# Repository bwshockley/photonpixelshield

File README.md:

Photon Pixel Shield
Photon Pixel Shield
========
The photon pixel shield is a small board for interfacing between a [particle.io](https://www.particle.io/) photon and some WS2812 based LED strips.  Specifically, this board was made to drive [Neopixel](https://www.adafruit.com/category/168) strips.

Power Requirements - Diode and Fuse Sizing
--------
The board takes in 5V only  and is used to power the photon and the pixel strip.  Please note that current requirements are mostly driven by the number of LEDs being driven.  Each WS2812 LED uses an estimate of 20mA, which can add up quickly.

50   Neopixels: 1A
100 Neopixels: 2A

You will need to pick your own diode and fuse.  Since these devices are through hole, physical sizing isn't as much of a concern for finding the right part - mostly the current/voltage ratings.  I found fuses and diodes up to 3A easily fit.  Find a Diode with a low forward voltage (less than 0.5V)

_Note that v6 does away with the diode, so no need to pick or size that and v7 does away with both the diode and fuse._

Digital Control
--------
The WS2812 based LED strips can be controlled via the photon and the [Neopixel library](https://github.com/technobly/SparkCore-NeoPixel) from Adafruit built by technobly.  No digital pin is selected by default on the board.  Pin D2 is the default in the library.  To use the default connect the solder jumper for D2 on the back of the board.  Otherwise, you may select almost any digital pin in both software on through the jumper on the board.

BOM
--------
The majority of the [BOM](http://www.mouser.com/ProjectManager/ProjectDetail.aspx?AccessID=84ec81cb7a), which as of 12-JUL-18, can be found on Mouser.com for around $3.50.  You will need to pick a diode and re-settable fuse as noted above.

Power LED
--------
A simple 3mm power LED is required if you wish to have a power indicator.  The resistor marked RLED on the board is for the LED.  Populate with an appropriate resistor value for the LED chosen.  You can use [this calculate](http://ledcalc.com) for sizing the resistor.

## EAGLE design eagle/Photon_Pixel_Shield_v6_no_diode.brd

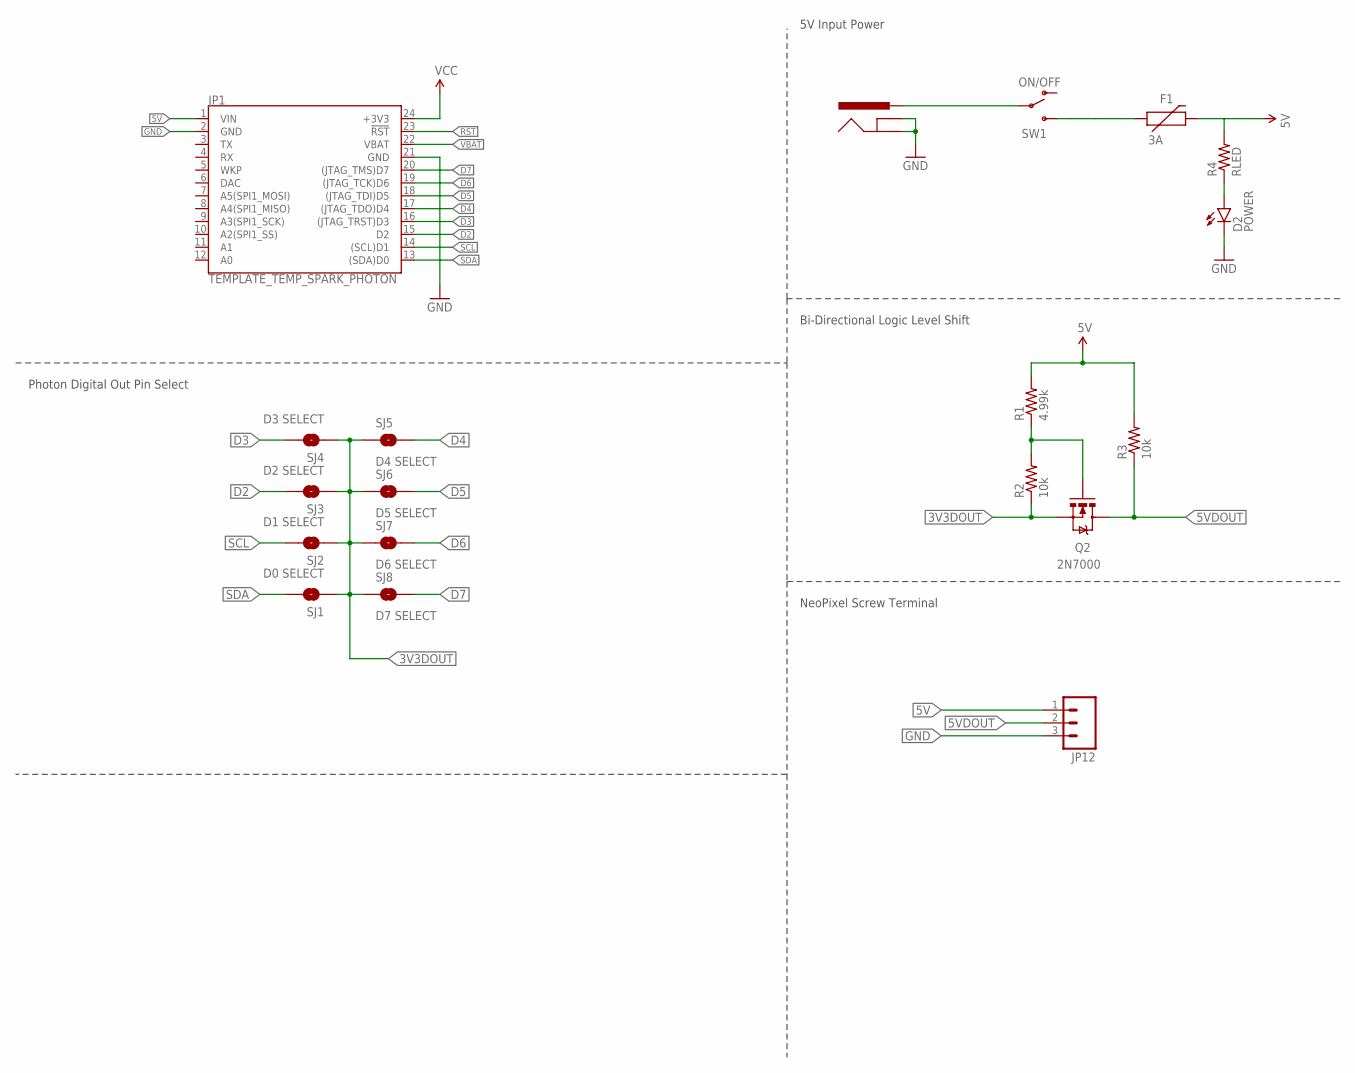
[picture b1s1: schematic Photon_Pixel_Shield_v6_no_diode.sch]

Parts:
D2: POWER; LED3MM
F1: 3A; PTC
J1: POWER_JACKPTH; POWER_JACK_PTH
JP1: TEMPLATE_TEMP_SPARK_PHOTON
JP12: M03SCREW; SCREWTERMINAL-3.5MM-3
Q2: 2N7000; TO-92
R1: 4.99k; AXIAL-0.3
R2, R3: 10k; AXIAL-0.3
R4: RLED; AXIAL-0.3
SJ1: D0 SELECT; SJ_2S-NO
SJ2: D1 SELECT; SJ_2S-NO
SJ3: D2 SELECT; SJ_2S-NO
SJ4: D3 SELECT; SJ_2S-NO
SJ5: D4 SELECT; SJ_2S-NO
SJ6: D5 SELECT; SJ_2S-NO
SJ7: D6 SELECT; SJ_2S-NO
SJ8: D7 SELECT; SJ_2S-NO
SW1: ON/OFF; SWITCH-SPST

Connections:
3V3DOUT: Q2.1 (S), R2.P$1 (1), SJ1.1, SJ2.1, SJ3.1, SJ4.1, SJ5.1, SJ6.1, SJ7.1, SJ8.1
5V: F1.P$2 (2), JP1.1 (VIN), JP12.1, R1.P$2 (2), R3.P$2 (2), R4.P$2 (2)
5VDOUT: JP12.2, Q2.3 (D), R3.P$1 (1)
D2: JP1.15 (D2), SJ3.2
D3: JP1.16 ((JTAG_TRST)D3), SJ4.2
D4: JP1.17 ((JTAG_TDO)D4), SJ5.2
D5: JP1.18 ((JTAG_TDI)D5), SJ6.2
D6: JP1.19 ((JTAG_TCK)D6), SJ7.2
D7: JP1.20 ((JTAG_TMS)D7), SJ8.2
GND: D2.K (C), J1.GND, J1.GNDBREAK, JP1.2 (GND), JP1.21 (GND), JP12.3
unnamed: F1.P$1 (1), SW1.3 (S)
unnamed: J1.PWR, SW1.2
unnamed: D2.A, R4.P$1 (1)
unnamed: Q2.2 (G), R1.P$1 (1), R2.P$2 (2)
RST: JP1.23 (!RST!)
SCL: JP1.14 ((SCL)D1), SJ2.2
SDA: JP1.13 ((SDA)D0), SJ1.2
VBAT: JP1.22 (VBAT)
VCC: JP1.24 (+3V3)

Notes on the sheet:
Bi-Directional Logic Level Shift
NeoPixel Screw Terminal
5V Input Power
Photon Digital Out Pin Select

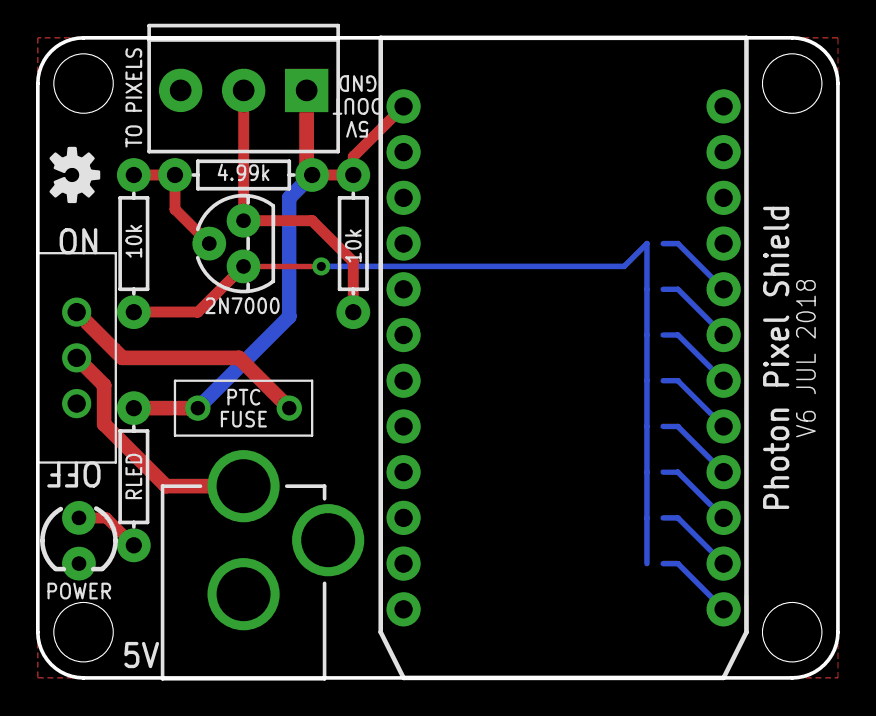
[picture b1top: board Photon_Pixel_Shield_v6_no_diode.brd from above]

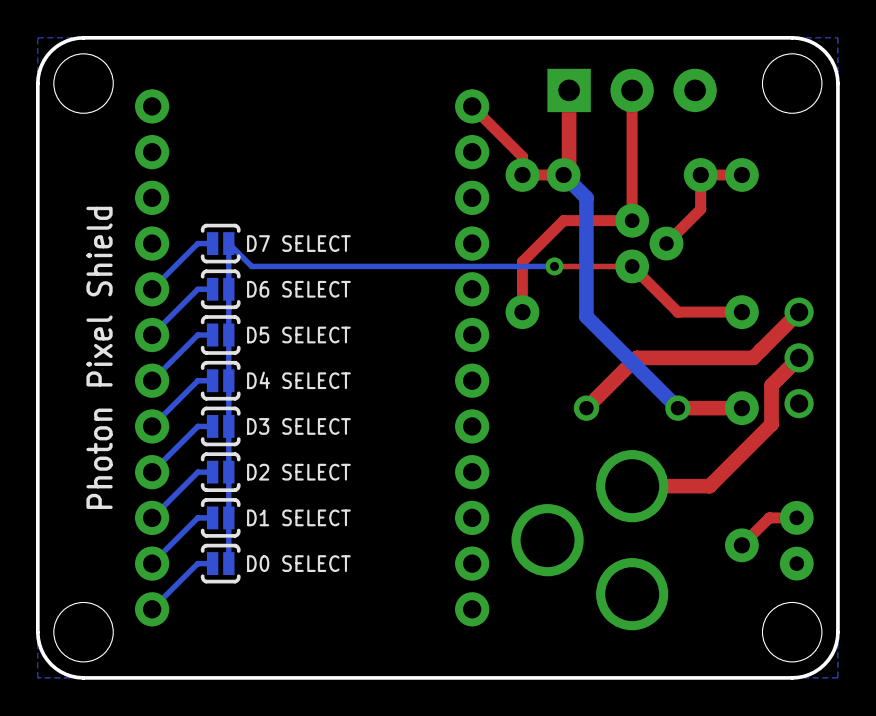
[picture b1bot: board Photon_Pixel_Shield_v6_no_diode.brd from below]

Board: 2 copper layers, 44.5 x 35.6 mm, 20 parts (8 on the bottom side), 16 nets.

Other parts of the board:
U$1: OSHW-LOGO-S

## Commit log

2016-03-18 Initialize README.md
    Added initial data to README.
2018-07-13 Added v5, v6, v7 to the repository.
    These versions are all similar.
2018-07-13 Updated to reflect v6, and v7 changes.
    Updated a few items for more detail and added info for v6 and v7

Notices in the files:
parts and their libraries:
SparkFun-Connectors: Licensing: Creative Commons ShareAlike 4.0 International - https://creativecommons.org/licenses/by-sa/4.0
